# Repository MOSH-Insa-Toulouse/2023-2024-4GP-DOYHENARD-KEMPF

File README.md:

# **4A GP - Projet "Du capteur au banc de test" - I4PMH21**

## **Sommaire**
+ [Objectif du projet](https://github.com/MOSH-Insa-Toulouse/2023-2024-4GP-DOYHENARD-KEMPF?tab=readme-ov-file#objectif-du-projet)
+ [Livrables](https://github.com/MOSH-Insa-Toulouse/2023-2024-4GP-DOYHENARD-KEMPF?tab=readme-ov-file#livrables)
+ [LTSpice](https://github.com/MOSH-Insa-Toulouse/2023-2024-4GP-DOYHENARD-KEMPF?tab=readme-ov-file#ltspice)
+ [KiCad](https://github.com/MOSH-Insa-Toulouse/2023-2024-4GP-DOYHENARD-KEMPF?tab=readme-ov-file#kicad)
+ [Shield](https://github.com/MOSH-Insa-Toulouse/2023-2024-4GP-DOYHENARD-KEMPF?tab=readme-ov-file#conception-du-shield)
+ [Code Arduino](https://github.com/MOSH-Insa-Toulouse/2023-2024-4GP-DOYHENARD-KEMPF?tab=readme-ov-file#code-arduino)
+ [Application Android](https://github.com/MOSH-Insa-Toulouse/2023-2024-4GP-DOYHENARD-KEMPF?tab=readme-ov-file#application-bluetooth-pour-android)
+ [Datasheet](https://github.com/MOSH-Insa-Toulouse/2023-2024-4GP-DOYHENARD-KEMPF?tab=readme-ov-file#datasheet-du-capteur-graphite)

## **Objectif du projet**
Dans le cadre d'un cours dispensé lors du 2<sup>nd</sup> semestre de 4<sup>ème</sup> année de Génie Physique à l'INSA de Toulouse, il nous a été proposé de réaliser un capteur low-tech à base de graphite, puis d'en faire une analyse critique argumentée pour en cerner les potentialités mais également pour évoquer des solutions d’amélioration. Ainsi, ce projet nous a permis de balayer l’ensemble du domaine : du capteur jusqu’à la réalisation d’une datasheet et du banc de test.

## **Livrables**
* Un shield PCB branché à une board Arduino UNO sur lequel nous retrouverons différents composants tels que :
  - Un capteur graphite
  - Un circuit d'amplification transimpédence
  - Un module Bluetooth
  - Un encodeur rotatoire
  - Un potentiomètre digital (_qui vient remplacer la résistance R2 du circuit d'amplifiaction_)
  - Un capteur de contrainte commercial

* Une simulation LTSpice du circuit transimpédence

* Un fichier KiCad du shield avec l'ensemble des composants cités en amont

* Un code Arduino qui gère le fonctionnement et les communications des 2 à 6 avec la board

* Un fichier APK Android (_conçue à l'aide du site MIT APP Inventor_) qui permet, à partir d'un smartphone Android, de gèrer l'interface avec le shield Arduino UNO par le biais d'une communication Bluetooth

* La datasheet du capteur graphite

## **LTSpice**
Nous avons réalisé une étude de notre circuit à l'aide du logiciel _LTSpice_. En effet, le capteur étudié ayant une résistance de l'ordre du GOhm, le courant délivré est alors trop faible (de l'ordre du nA). Pour qu'il puisse être exploitable, ce signal en courant doit donc être **filtré** de tout bruit parasite puis **amplifié**. C'est précisément le rôle du montage suivant :

_Circuit d'amplification/atténuation_

_Modélisation du capteur_

Ce montage se compose de 3 filtres passe-bas distincts :
- Un 1<sup>er</sup> formé par R<sub>5</sub>, C<sub>1</sub> et R<sub>1</sub>, filtrant les bruits en courant sur le signal d'entrée causés par l’alimentation 5V symbolisé par le 'SINE' + C<sub>3</sub>
- Un 2<sup>nd</sup> formé par C<sub>4</sub> et R<sub>3</sub>, pour réduire la composante de bruit à 50 Hz induite par réseau électrique ambiant
- Un 3<sup>ème</sup> formé par R<sub>6</sub> et C<sub>2</sub>, placé à la sortie de l'amplificateur qui atténue le bruit intrinsèque du circuit

Grâce à ce montage, nous sommes capable de mesurer la résistance du capteur graphite en suivant la formule suivante : $`R_{Meas} = \frac{V_{CC}}{V_{ADC}}*R_1*(1+\frac{R_3}{R_{potentio}})-R_1-R_5`$

Afin de nous assurer que notre circuit jouait bien le rôle de filtreur/amplificateur, nous avons réalisé 2 simulation : une qui vérifiera la correcte amplification du signal en sortie de circuit, l'autre qui permettra de confirmer la bonne atténuation du signal pour des fréquences non souhaitées :

Nous voyons ici que le signal de sortie est de 1V, soit un ordre de grandeur tout à fait mesurable et donc exploitable dans notre cas.

Ici, nous avons simulé un courant alternatif grâce auquel il nous sera possible d'observer la réduction du bruit : Nous observons une atténuation d'environ 46 dB à 50 Hz. Le comportement global du circuit est bel est bien passe-bas.

--> La simulation LTSpice est donc conforme aux attentes.

## **KiCad**
Afin de construire un shield PCB qui respecte à la fois les consignes mentionnées dans le document _INSTRUCTIONS for the UF “From the sensor to the test bench” – I4PMH21_ ainsi que les contraintes électroniques, mécaniques et physiques des composants qu'il supportera, il nous a fallu élaborer une maquette virtuelle de ce dernier via le logiciel _KiCad_. Nous avons donc dans un 1<sup>er</sup> temps réalisé une 'schematic' de l'ensemble des composants impliqués :

Nous avons en suite utilisé la partie _PCB_ du logiciel afin de disposer les différents composants sur le shield, en tenant compte de la contrainte liée aux masses, qui doivent être réliées indirectement entre elles via le plan de masse. Nous sommes arrivés au résultat suivant :

Nous avons également effectué un rendu 3D de notre shield afin d'en avoir un 1<sup>er</sup> aperçu 'réaliste', dont voici un cliché pris du dessus :

## **Conception du shield**
Après validation de notre travail sur _KiCad_ par nos responsables, nous avons procédé à la confection réelle de notre shield, fabriqué à partir d'une plaquette d’époxy recouverte d’une fine couche de cuivre.
Les principales étapes de fabrication sont :
- Une insolation aux UVs de la plaquette grâce au calque modélisé dans la partie PCB de _KiCad_.
- Le retrait de la résine non isolée à l'aide d'un révélateur.
- Le placement de la plaquette dans une solution de percholorure de fer.

A la suite de cela, avons pu assembler les composants sur la plaquette. Pour cela, il a fallu respecter les consignes à appliquer que ce soit au niveau du perçage de la plaquette ou bien du soudage des composants :

> [!NOTE]
> Nous avons finalement décidé de ne pas nous servir de Servomoteur du fait d'un manque de temps.

## **Code Arduino**
En parallèle de la partie _KiCad_, nous nous sommes attelés à la programmation du **[code Arduino](https://github.com/MOSH-Insa-Toulouse/2023-2024-4GP-DOYHENARD-KEMPF/blob/main/Code%20Arduino/Code_V_Finale.c)** qui permettra la commuication de chacun des composants entre eux mais aussi avec l'Arduino UNO, ainsi qu'avec un smartphone via l'application Android.

## **Application Bluetooth pour Android**
Nous avons réalisé une **[application Android](https://github.com/MOSH-Insa-Toulouse/2023-2024-4GP-DOYHENARD-KEMPF/tree/main/Application%20Android)** à l'aide du site _MIT App Inventor_. Cette application permet de lire les valeurs des capteurs en temps réel, mais aussi de les stocker pour établir des courbes de variation de résistance en fonction de la déformation qui leur est appliquée : 

## **Datasheet du capteur graphite**
La rédaction de la datasheet induit plusieurs tests préalables de nos capteurs. Pour ce faire, nous nous sommes servis d'un banc de test imprimé en 3D, composé de 7 demi-disques allant de 1cm à 5cm de diamètre. Les capteurs quant à eux, ont tous les mêmes dimensions, mais sont usinés avec différents type de crayons à papier, allant du H au B en passant par le F et comprenant nombre de leur dérivées (HB, 2H, 4H, 4B et 6B dans notre cas) :

Nous avons ainsi effectué plusieurs mesures pour chaque type de crayon, ainsi que pour le flex sensor commercial avec lequel nous comparerons nos résultats : 
- Mesure de résistance à plat
- Série de mesure de résistance avec une déformation en **extension** en suivant certains demi-disques sélectionnés.
- Série de mesure de résistance avec une déformation en **compression** avec les mêmes demi-disques.

> [!NOTE]
> Des valeurs incohérentes ont été observées pour certains capteurs. Nous avons donc décidé de ne pas les retenir dans nos résultats finaux.

--> Nous avons pu par la suite établir des graphes montrant la variation relative de résistance des différents capteurs en fonction de la déformation subie (compression ou extension, à divers degré d'intensité) que l'on retrouve dans la **[datasheet](https://github.com/MOSH-Insa-Toulouse/2023-2024-4GP-DOYHENARD-KEMPF/blob/main/Datasheet/%5BDataheet%5D%20-%20Pencil-Drawn%20Strain%20Gauge.pdf)** de nos capteurs graphite.

> [!WARNING]
> Les mesures ayant été difficiles, du fait d'une faible reproductibilité induite par des paramètres variants (densité de graphite au cours du temps, faux-contact électrique détecté en fin de prise de mesures), les résultats en valeurs absolues n'ont pas répondu à nos exigeances. Il nous a donc fallu nous appuyer sur l'aide de [collègues INSAïens](https://github.com/MOSH-Insa-Toulouse/2022-2023-Conan-Pistre) de la promo 2024, sans qui les courbes de mesures ne figureraient pas.

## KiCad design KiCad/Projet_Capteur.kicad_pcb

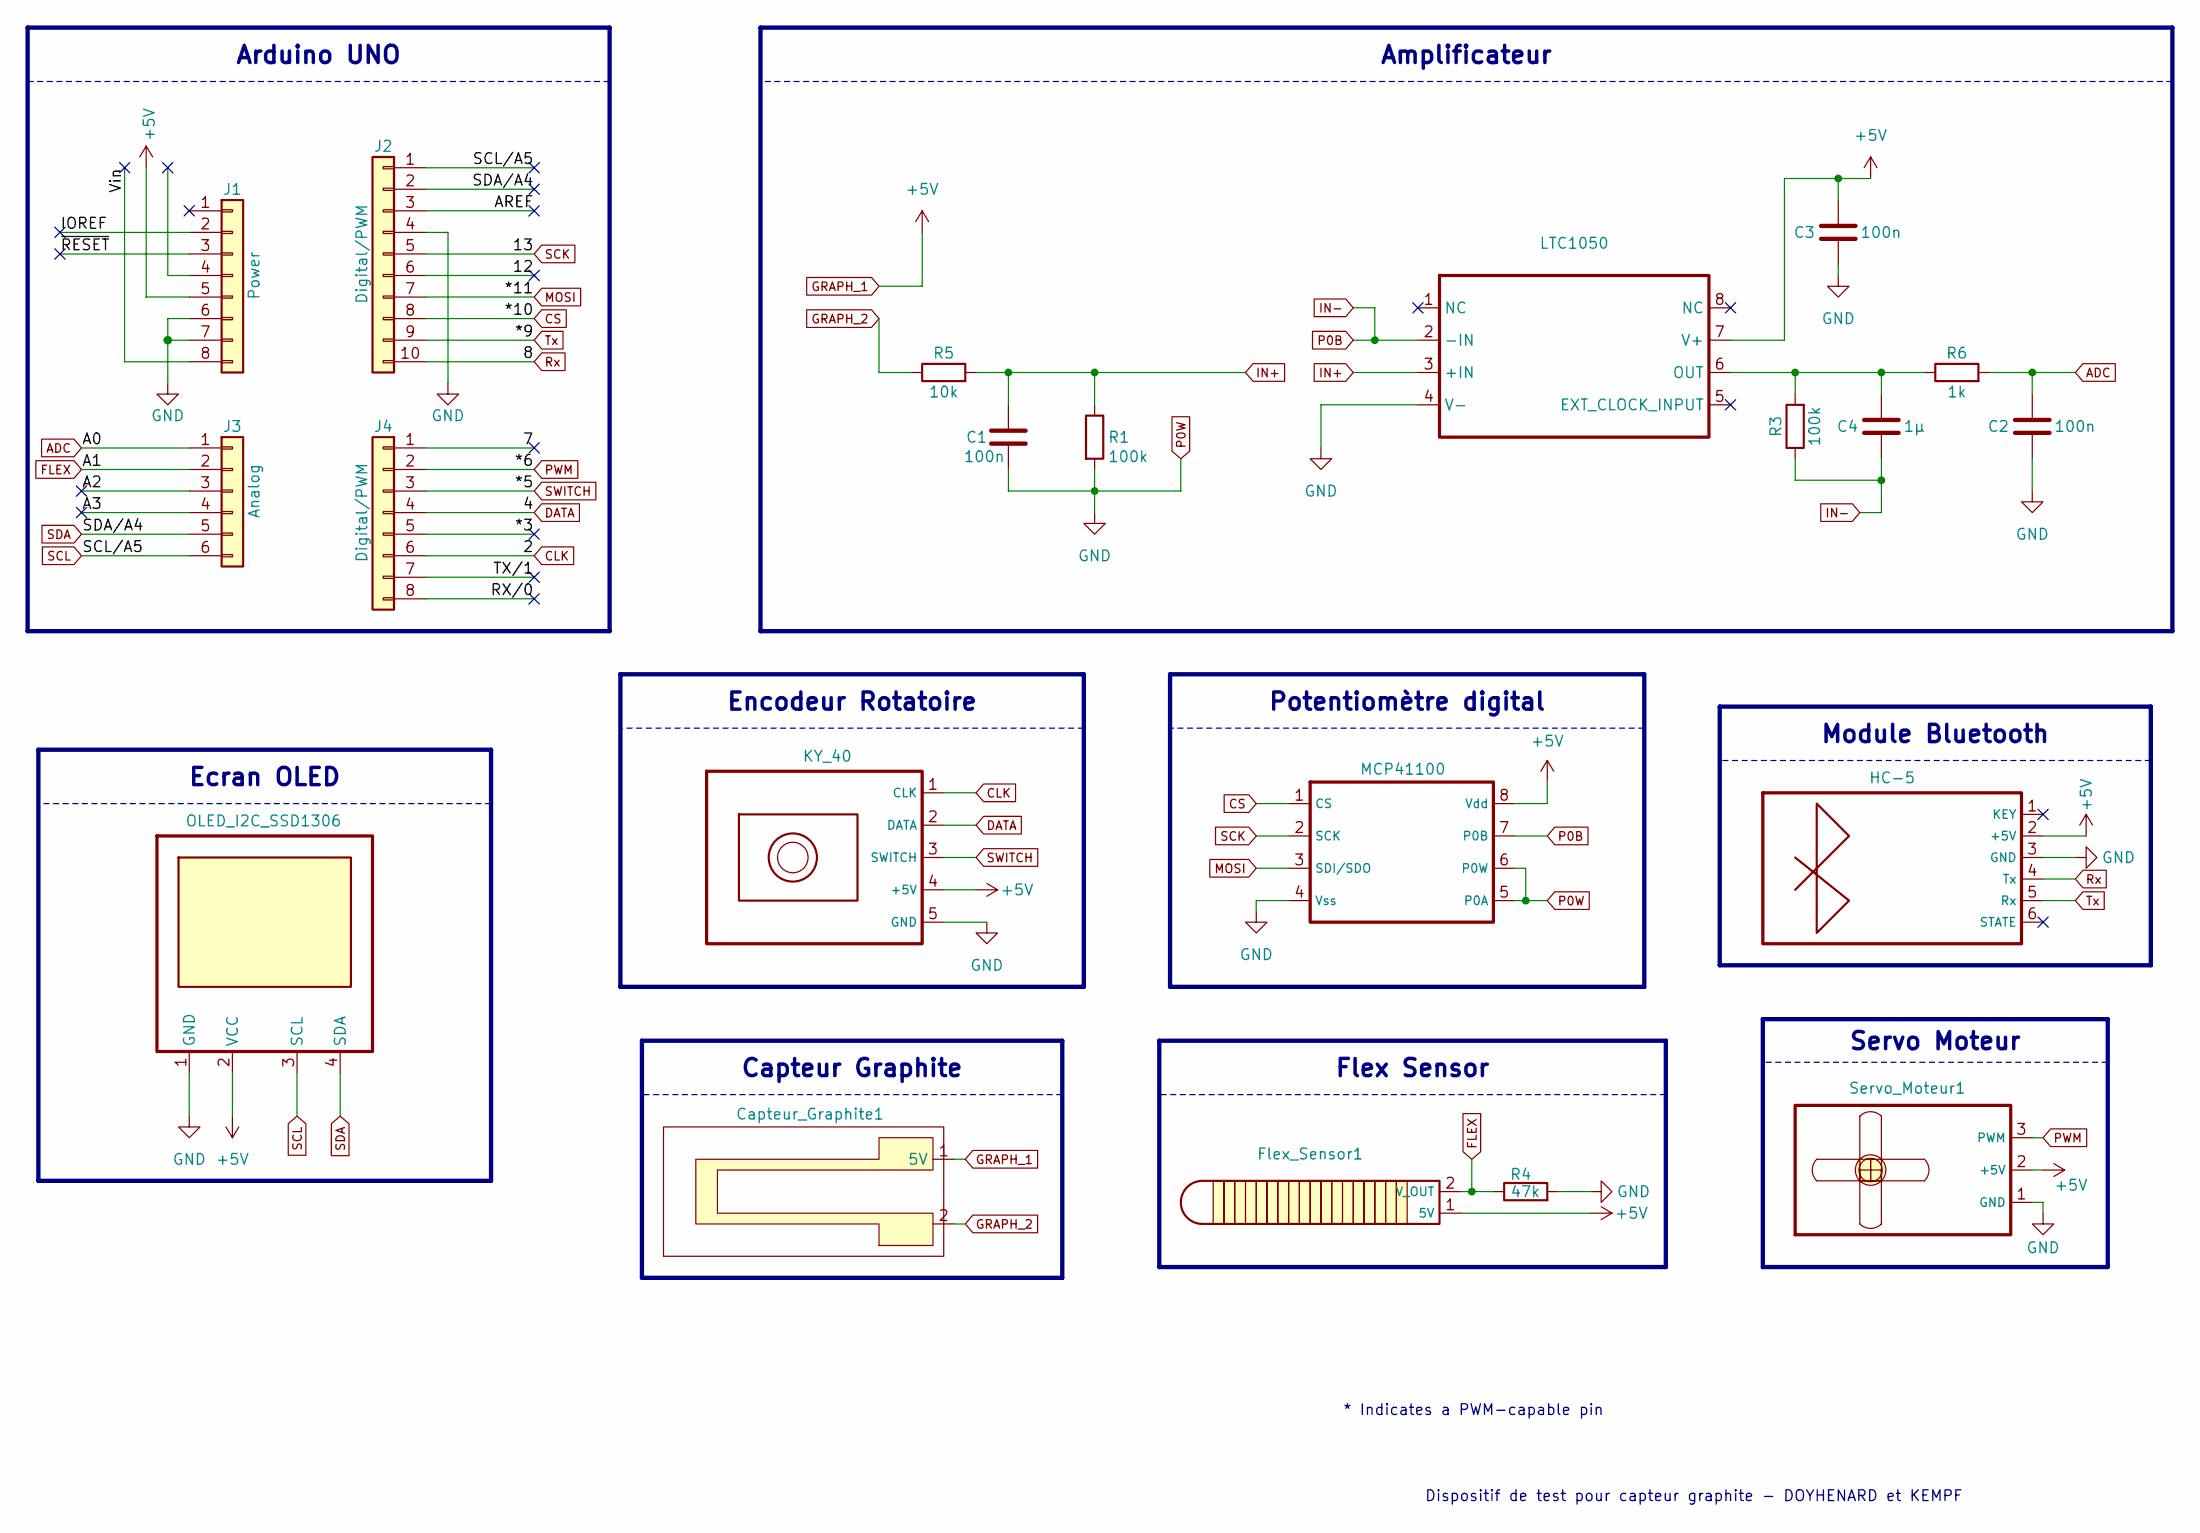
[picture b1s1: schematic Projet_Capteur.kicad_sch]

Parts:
C1, C2, C3: 100n; R_ou_C_a_100n
C4: 1µ; C_Rect_L7.0mm_W4.5mm_P5.00mm
Capteur_Graphite1: Sensor
Flex_Sensor1: Sensor
HC-5: HC-05 (Bluetooth)
J1: Power; PinSocket_1x08_P2.54mm_Vertical
J2: Digital/PWM; PinSocket_1x10_P2.54mm_Vertical
J3: Analog; PinSocket_1x06_P2.54mm_Vertical
J4: Digital/PWM; PinSocket_1x08_P2.54mm_Vertical
KY_40: Encodeur KY_040
LTC1050: DIP-8_W7.62mm_LongPads
MCP41100: DIP-8_W7.62mm_LongPads
OLED_I2C_SSD1306: OLED SSD1306
R1, R3: 100k; R_ou_C_a_100n
R4: 47k; R_ou_C_a_100n
R5: 10k; R_ou_C_a_100n
R6: 1k; R_ou_C_a_100n
Servo_Moteur1: Servo Moteur

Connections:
/7: J4.1
/12: J2.6
/*3: J4.5
/A2: J3.3
/A3: J3.4
/AREF: J2.3
/IOREF: J1.2
/RX/0: J4.8
/TX/1: J4.7
/Vin: J1.8
/~RESET: J1.3
ADC: C2.1, J3.1, R6.2
CLK: J4.6, KY_40.1 (CLK)
CS: J2.8, MCP41100.1 (CS)
DATA: J4.4, KY_40.2 (DATA)
FLEX: Flex_Sensor1.2 (V_OUT), J3.2, R4.1
GRAPH_1: C3.1, Capteur_Graphite1.1 (5V), Flex_Sensor1.1 (5V), HC-5.2 (+5V), J1.5, KY_40.4 (+5V), LTC1050.7 (V+), MCP41100.8 (Vdd), OLED_I2C_SSD1306.2 (VCC), Servo_Moteur1.2 (+5V)
GRAPH_2: Capteur_Graphite1.2, R5.1
IN+: C1.1, LTC1050.3 (+IN), R1.1, R5.2
IN-: C4.2, LTC1050.2 (-IN), MCP41100.7 (P0B), R3.1
MOSI: J2.7, MCP41100.3 (SDI/SDO)
unnamed: C4.1, LTC1050.6 (OUT), R3.2, R6.1
P0W: C1.2, C2.2, C3.2, HC-5.3 (GND), J1.6, J1.7, J2.4, KY_40.5 (GND), LTC1050.4 (V-), MCP41100.4 (Vss), MCP41100.5 (P0A), MCP41100.6 (P0W), OLED_I2C_SSD1306.1 (GND), R1.2, R4.2, Servo_Moteur1.1 (GND)
PWM: J4.2, Servo_Moteur1.3 (PWM)
Rx: HC-5.4 (Tx), J2.10
SCK: J2.5, MCP41100.2 (SCK)
SCL: J2.1, J3.6, OLED_I2C_SSD1306.3 (SCL)
SDA: J2.2, J3.5, OLED_I2C_SSD1306.4 (SDA)
SWITCH: J4.3, KY_40.3 (SWITCH)
Tx: HC-5.5 (Rx), J2.9

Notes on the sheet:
Module Bluetooth
Flex Sensor
Potentiomètre digital
Servo Moteur
Encodeur Rotatoire
Arduino UNO
Capteur Graphite
Amplificateur
Ecran OLED
* Indicates a PWM-capable pin
Dispositif de test pour capteur graphite - DOYHENARD et KEMPF

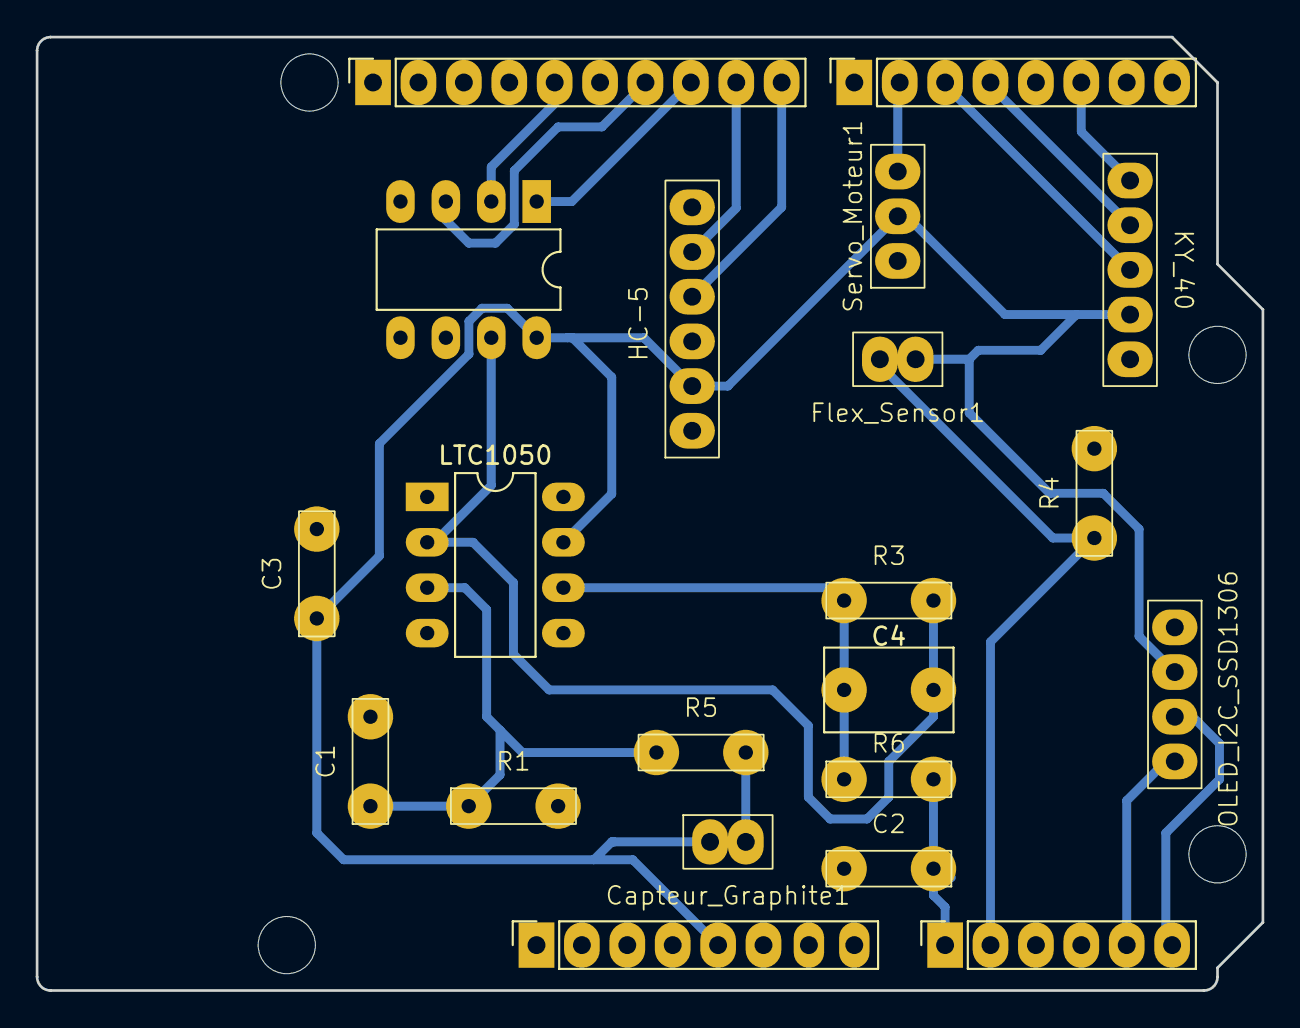
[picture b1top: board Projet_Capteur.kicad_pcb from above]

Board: 2 copper layers, 68.6 x 53.3 mm, 25 parts (0 on the bottom side), 19 nets.

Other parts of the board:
MH1, MH2, MH3, MH4: MountingHole_3.2mm

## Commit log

2024-04-13 Update README.md
    Début de rédaction
2024-04-13 Create Partie PCB
2024-04-13 Create ok
2024-04-13 Create lol
2024-04-13 Create oui
2024-04-13 Create swagman
2024-04-13 Create wow
2024-04-13 Create oh
2024-06-05 Create android
2024-06-06 Create o
